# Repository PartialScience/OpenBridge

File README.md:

# OpenBridge

An open-source eight-IGBT full-bridge power stage for DRSSTC/Tesla-coil builds, designed in KiCad 10. It uses an external gate driver and DC supply, with two off-board gate-drive transformers and a Wakefield 511-6M heatsink.

| Schematic | PCB layout |
| :---: | :---: |
|  |  |

The 3D preview shows the main board after removing the four breakaway GDT strips. The PCB layout shows the complete fabrication board, with blue bottom copper beneath red top copper. Click either drawing for the full-size view.

## Project files

Open **[OpenBridge.kicad_pro](OpenBridge.kicad_pro)** in KiCad 10 or newer with the standard symbol, footprint and 3D-model libraries installed. Custom parts and STEP models are included in `OpenBridge.pretty`, `OpenBridge.kicad_sym` and `OpenBridge.3dshapes`.

The [Hardware subsheet](Hardware.kicad_sch) collects the heatsink, IGBT insulators, shoulder washers, spacers, cable connectors and assembly hardware. See its [drawing](docs/images/hardware.svg), the [BOM for one board](docs/bom.csv), and [assembly/BOM notes](docs/assembly.md).

GDT winding details, wire sizes, fastener lengths and other coil-dependent choices are **unspecified**. The BOM includes generic assembly materials; it does not define a complete coil, gate driver, power supply, fan or enclosure. Component ratings are not a validated operating rating for the assembled bridge.

## PCB fabrication

Fabrication specification for JLCPCB. Physical parameters are saved in `OpenBridge.kicad_pcb` under **Board Setup → Board Stackup → Physical Stackup / Board Finish**; via tenting is under **Solder Mask/Paste**.

| Setting | Specification |
| --- | --- |
| Construction | 2-layer FR-4, Tg135, 1.6 mm overall thickness |
| Copper | 2 oz on both sides, modeled as 0.070 mm (70 µm) per layer |
| Solder mask / silkscreen | Black / white |
| Surface finish | HASL with lead (`HAL SnPb` in KiCad) |
| Via covering | Tented on both sides |
| Nominal board outline | 116.84 × 167.64 mm, defined by Edge.Cuts |

Manufacturing requirements: **IPC Class 2**, **full flying-probe electrical testing**, and **±0.2 mm outline tolerance**. Select these with the fabricator when ordering.

The nominal stackup models a 1.44 mm FR-4 core and 0.01 mm solder mask per side. Dielectric constant (4.5) and loss tangent (0.02) are estimates pending manufacturer laminate data. Confirm the copper weight, laminate grade and finish with the fabricator.

## Update the previews

With Python 3.10+ and KiCad 10+ installed, run from the repository:

```sh
python scripts/update_previews.py
```

This audits the BOM and regenerates all README images from the saved design. Add `--watch` to refresh after saves while editing. The script uses a temporary board copy and isolated rendering settings, so it does not modify the manufacturing PCB or global KiCad preferences.

Set `board_color` in **[scripts/render-config.json](scripts/render-config.json)** to change the 3D solder mask. It defaults to `Black`; named KiCad colors and `#RRGGBB` are supported. The same file controls camera angle, image size and breakaway-strip removal. Run the script again after changing it.

KiCad is found automatically on Windows or through `PATH`. Set `KICAD_CLI` if needed, and `KICAD10_3DMODEL_DIR` if the standard models are installed elsewhere. Run `python scripts/check_bom.py` for the BOM audit/export alone.

The included [GitHub workflow](.github/workflows/previews.yml) refreshes and commits images/BOM after design changes are pushed to `main`, using the [official KiCad container](https://www.kicad.org/download/docker/). It needs Actions enabled and permission to push generated files; with branch protection, regenerate locally and include them in your normal review. The checked-in images also work offline.

## Contributing and license

Keep the schematic as the source of truth for parts, update the PCB from it when needed, and regenerate previews/BOM with design changes. Run KiCad ERC and DRC before proposing a change, and review all findings before fabrication. See the [assembly notes](docs/assembly.md) for component selection and validation guidance.

See [LICENSE](LICENSE) for the repository's GPL-3.0 license. Third-party libraries, datasheets and manufacturer models retain their applicable terms.

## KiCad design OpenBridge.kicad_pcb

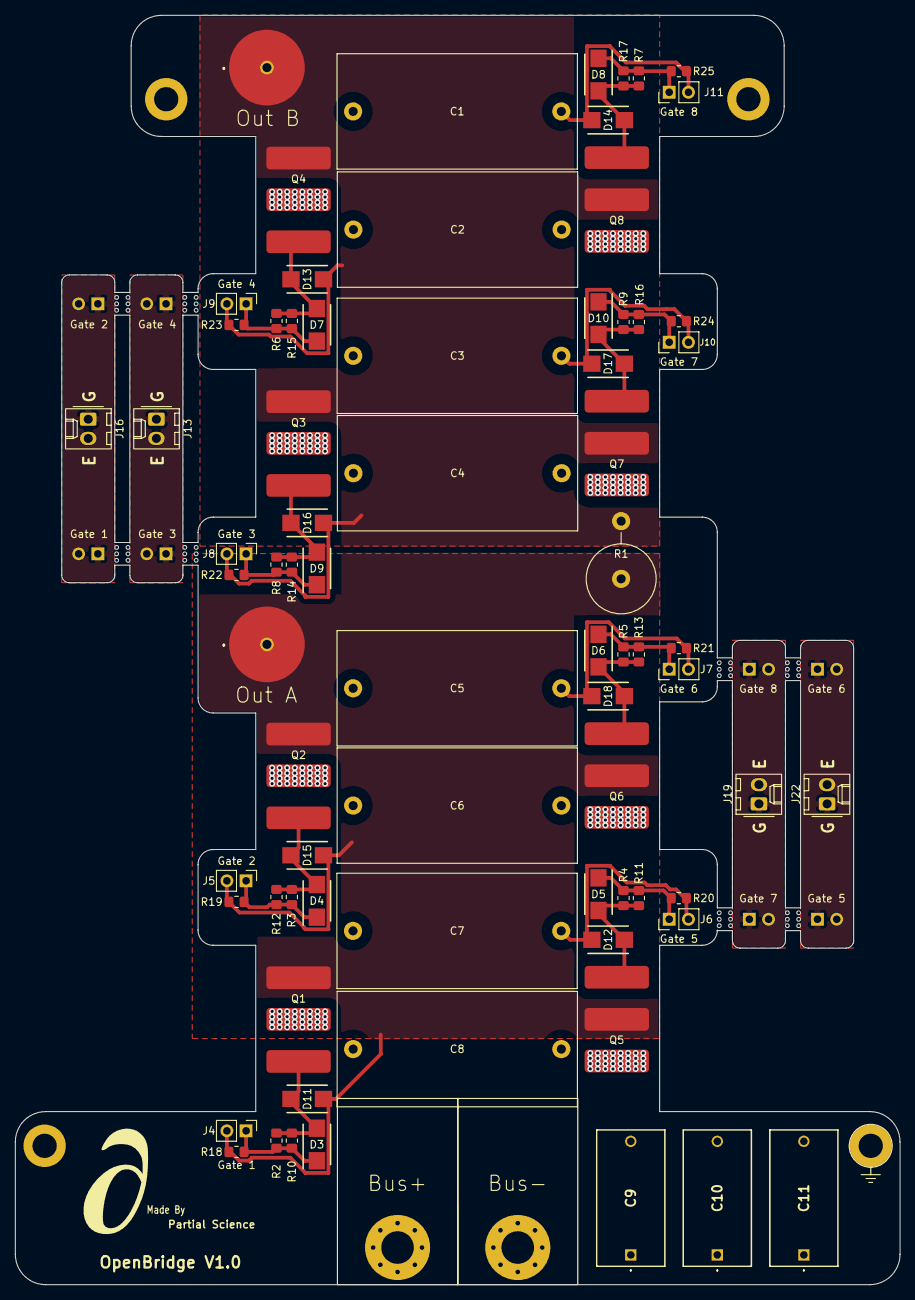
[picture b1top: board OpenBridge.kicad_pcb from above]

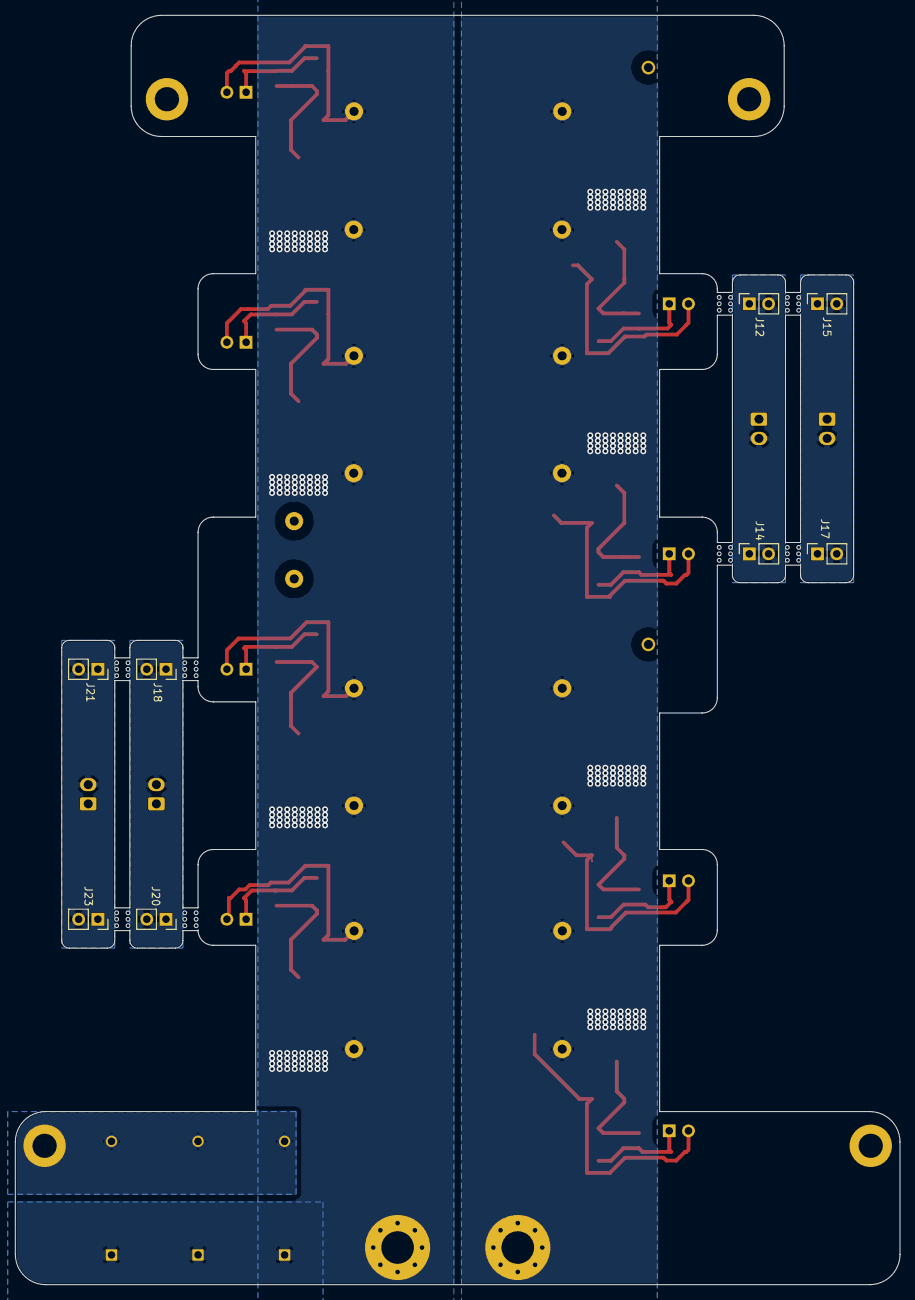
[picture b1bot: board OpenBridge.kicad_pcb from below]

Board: 2 copper layers, 116.8 x 167.6 mm, 105 parts (8 on the bottom side), 29 nets.

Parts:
C1, C2, C3, C4, C5, C6, C7, C8: 7uF; C_Rect_L31.5mm_W15.0mm_P27.50mm_KEMET_C4AQ
C9, C10, C11: 4.7nF; C_Rect_L18.0mm_W9.0mm_P15.00mm_TDK_B81123
D3, D4, D5, D6, D7, D8, D9, D10: SSB44; DIOM5436X265N
D11, D12, D13, D14, D15, D16, D17, D18: SMBJ24CA; DIONM5336X265N
H1, H2: MountingHole_Pad; MountingHole_4.3mm_M4_Pad_Via
H5, H6, H7, H8: MountingHole_Pad; MountingHole_3.2mm_M3_DIN965_Pad
HS1: 511-6M; Heatsink_Wakefield_511-6M
J1, J2: 7466105
J4, J5, J6, J7, J8, J9, J10, J11: Conn_01x02; PinHeader_1x02_P2.54mm_Vertical
J12, J14, J15, J17, J18, J20, J21, J23: Conn_01x02; PinSocket_1x02_P2.54mm_Vertical
J13, J16, J19, J22: Conn_01x02; Molex_KK-254_AE-6410-02A_1x02_P2.54mm_Vertical
MB1, MB2, MB3, MB4, MB5, MB6, MB7, MB8, MB9, MB10, MB11, MB12, MB13, MB14, MB15, MB16: MouseBite; BreakLine_3h_D0.5mm_P0.85mm
Q1, Q2, Q3, Q4, Q5, Q6, Q7, Q8: FGH75T65SHD-F155; TO-247-3_onsemi-340CH_Horizontal_TabUp_ScrewAccess
R1: 10k; R_Axial_DIN0922_L20.0mm_D9.0mm_P7.62mm_Vertical
R2, R3, R4, R5, R6, R7, R8, R9, R10, R11, R12, R13, R14, R15, R16, R17: 9.1; R_0805_2012Metric_Pad1.20x1.40mm_HandSolder
R18, R19, R20, R21, R22, R23, R24, R25: 10k; R_0805_2012Metric_Pad1.20x1.40mm_HandSolder

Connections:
/BS1_E: J12.2, J13.2, J14.2
/BS1_G: J12.1, J13.1, J14.1
/BS2_E: J15.2, J16.2, J17.2
/BS2_G: J15.1, J16.1, J17.1
/BS3_E: J18.2, J19.2, J20.2
/BS3_G: J18.1, J19.1, J20.1
/BS4_E: J21.2, J22.2, J23.2
/BS4_G: J21.1, J22.1, J23.1
/Bus+: C1.1, C2.1, C3.1, C4.1, C5.1, C6.1, C7.1, C8.1, H1.1 (1_1), Q1.2 (C), Q2.2 (C), Q3.2 (C), Q4.2 (C)
/Bus-: C1.2, C2.2, C3.2, C4.2, C5.2, C6.2, C7.2, C8.2, C9.1, C10.1, C11.1, D12.1 (A1), D14.1 (A1), D17.1 (A1), D18.1 (A1), H2.1 (1_1), J6.2, J7.2, J10.2, J11.2, Q5.3 (E), Q6.3 (E), Q7.3 (E), Q8.3 (E), R20.1, R21.2, R24.1, R25.2
/G1: D3.2 (A), D11.2 (A2), Q1.1 (G), R2.2, R10.2
/G2: D4.2 (A), D15.2 (A2), Q2.1 (G), R3.2, R12.2
/G3: D9.2 (A), D16.2 (A2), Q3.1 (G), R8.1, R14.1
/G4: D7.2 (A), D13.2 (A2), Q4.1 (G), R6.1, R15.1
/G5: D5.2 (A), D12.2 (A2), Q5.1 (G), R4.2, R11.2
/G6: D6.2 (A), D18.2 (A2), Q6.1 (G), R5.2, R13.2
/G7: D10.2 (A), D17.2 (A2), Q7.1 (G), R9.1, R16.1
/G8: D8.2 (A), D14.2 (A2), Q8.1 (G), R7.1, R17.1
/GDT1_A: D3.1 (K), J4.1, R2.1, R10.1, R18.2
/GDT2_A: D7.1 (K), J9.1, R6.2, R15.2, R23.1
/GDT3_A: D5.1 (K), J6.1, R4.1, R11.1, R20.2
/GDT4_A: D8.1 (K), J11.1, R7.2, R17.2, R25.1
/OutA: D11.1 (A1), D15.1 (A1), J1.1 (Pin_1_1), J4.2, J5.2, Q1.3 (E), Q2.3 (E), Q5.2 (C), Q6.2 (C), R1.1, R18.1, R19.2
/OutB: D13.1 (A1), D16.1 (A1), J2.1 (Pin_1_1), J8.2, J9.2, Q3.3 (E), Q4.3 (E), Q7.2 (C), Q8.2 (C), R1.2, R22.1, R23.2
Heat Sink: C9.2, C10.2, C11.2, H5.1 (1_1)
unnamed: D4.1 (K), J5.1, R3.1, R12.1, R19.1
unnamed: D6.1 (K), J7.1, R5.1, R13.1, R21.1
unnamed: D9.1 (K), J8.1, R8.2, R14.2, R22.2
unnamed: D10.1 (K), J10.1, R9.2, R16.2, R24.2

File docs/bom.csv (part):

References,Quantity,Value,Manufacturer,MPN,Footprint,Description,Mouser,Datasheet
"C1, C2, C3, C4, C5, C6, C7, C8",8,7uF,KEMET,C4AQCBU4700A1YJ,OpenBridge:C_Rect_L31.5mm_W15.0mm_P27.50mm_KEMET_C4AQ,"Film capacitor, 7 uF 5 %, 650 VDC, metallized polypropylene DC-link, 27.5 mm pitch, 14 x 28 x 31.5 mm (KEMET C4AQ). Bridge bus decoupling",80-C4AQCBU4700A1YJ,https://www.mouser.com/datasheet/3/508/1/KEM_F3114_C4AQ.pdf
"C9, C10, C11",3,4.7nF,TDK,B81123C1472M000,OpenBridge:C_Rect_L18.0mm_W9.0mm_P15.00mm_TDK_B81123,"Y1 safety capacitor, 4.7 nF 20 %, 500 VAC, MKP film, 15 mm pitch, 9.0 x 17.5 x 18.0 mm (TDK B81123). Bus negative to RF ground. M000 = untaped, 6 mm leads; M289 is the same part on ammo tape",871-B81123C1472M,https://www.tdk-electronics.tdk.com/inf/20/20/db/fc_2009/Y1_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
"D3, D4, D5, D6, D7, D8, D9, D10",8,SSB44,Taiwan Semiconductor,SSB44,OpenBridge:DIOM5436X265N,"Schottky rectifier, 40 V, 4 A, SMB (DO-214AA). Pin 1 = K, pin 2 = A",821-SSB44,https://www.taiwansemi.com/assets/uploads/datasheet/SSB44_B2102.pdf
"D11, D12, D13, D14, D15, D16, D17, D18",8,SMBJ24CA,SEMTECH,SMBJ24CA,OpenBridge:DIONM5336X265N,"Bidirectional TVS diode, 24 V standoff, 600 W, SMB (DO-214AA). ESD Suppressors / TVS Diodes 1-Line 24V 15.4A TVS",947-SMBJ24CA,https://semtech.my.salesforce.com/sfc/p/E0000000JelG/a/2R000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
HS1,1,511-6M,Wakefield Thermal,511-6M,OpenBridge:Heatsink_Wakefield_511-6M,"Wakefield 511-6M aluminum heatsink, 152.4 mm long; board mounted on 3 mm spacers. Project STEP model and mechanical envelope; no PCB pads.",567-511-6M,https://wakefieldthermal.com/content/data_sheets/2021_data_s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
"HW1, HW2, HW3, HW4, HW5, HW6",6,22-01-2027,Molex,22-01-2027,,"KK 254 crimp housing 1x02, 2.54 mm, with friction ramp (Molex 2695). Wire-side mate of the GDT headers J13/J16/J19/J22",538-22-01-2027,
"HW7, HW8, HW9, HW10, HW11, HW12, HW13, HW14, HW15, HW16, HW17, HW18",12,08-50-0114,Molex,08-50-0114,,"KK 254 crimp terminal, female, 22-30 AWG, tin (Molex 2759). 2 per KK housing; buy spares for crimping",538-08-50-0114,
"HW19, HW20, HW21, HW22, HW23, HW24, HW25, HW26",8,60-11-D401-1671,Parker Chomerics,60-11-D401-1671,,"Thermal insulator pad, TO-247, 1.41 x 0.81 in, 0.015 in thick (Chomerics). 1 per IGBT (Q1-Q8)",24-60-11-D401-1671,
"HW27, HW28, HW29, HW30",4,M0592-3-N,RAF Electronic Hardware,M0592-3-N,,"Round spacer, M3 (3.2 mm ID), 3 mm long (RAF). Board to heat sink at H5-H8",761-M0592-3-N,
"HW31, HW32, HW33, HW34, HW35, HW36, HW37, HW38",8,3049,Keystone Electronics,3049,,"Shoulder washer #4, nylon 6/6 (Keystone 3049): 2.9 mm ID, 3.43 mm shoulder, 5.5 mm flange. Insulates each IGBT's 4-40 screw from its collector tab",534-3049,https://www.mouser.com/datasheet/3/201/1/3049.pdf
"HW39, HW40, HW41, HW42, HW43, HW44, HW45, HW46",8,#4-40 screw,Generic,Unspecified,,"IGBT-to-heatsink screw, #4-40; one per Q1-Q8, used with HW31-HW38 shoulder washers. Length, head style and tapped-hole depth unspecified; select for the assembled stack.",,
"HW47, HW48, HW49, HW50",4,M3 screw,Generic,Unspecified,,"Board-to-heatsink screw, M3; one per H5-H8 with 3 mm spacers. Length and head style unspecified; select for PCB thickness, spacer and tapped-hole engagement.",,
"HW51, HW52",2,M5 screw,Generic,Unspecified,,"Output ring-lug clamp screw, M5, one per J1/J2. Length unspecified; choose for lug/washer stack and <=4 mm thread engagement without bottoming in the REDCUBE blind hole.",,
"HW53, HW54",2,M5 flat washer,Generic,Unspecified,,"Flat washer, M5, one per J1/J2 output ring-lug clamp. Material and outside diameter unspecified.",,
"HW55, HW56",2,M5 ring terminal,Generic,Unspecified,,"Output cable ring terminal, M5 stud, one per J1/J2. Wire gauge, current rating and insulation unspecified; select for the coil build.",,
HW57,1,Power wire (lot),Generic,Unspecified,,"One assembly lot of power cable. Conductor gauge, insulation rating, length and termination details unspecified; selected for the coil build.",,
"HW58, HW59",2,M4 bolt,Generic,Unspecified,,"DC-input ring-lug clamp bolt, M4, one per H1/H2. Bolt length and head style unspecified; select for lug, PCB and washer stack.",,
"HW60, HW61",2,M4 nut,Generic,Unspecified,,"Nut, M4, one per H1/H2 DC-input bolt. Material and locking method unspecified.",,
"HW62, HW63, HW64, HW65",4,M4 flat washer,Generic,Unspecified,,"Flat washer, M4, two per H1/H2 DC-input bolt to distribute clamp load. Outside diameter and material unspecified.",,
"HW66, HW67",2,M4 ring terminal,Generic,Unspecified,,"DC-input cable ring terminal, M4 stud, one per H1/H2. Wire gauge, current rating and insulation unspecified; select for the coil build.",,
HW68,1,GDT wire (lot),Generic,Unspecified,,"One assembly lot of GDT winding and lead wire for T1/T2. Turns, ratio, phasing, wire gauge, insulation and length unspecified; selected for the coil build. T1/T2 BOM entries supply the bare cores only.",,
HW69,1,Insulation (lot),Generic,Unspecified,,"One assembly lot of heat-shrink/insulating sleeving for wiring and terminations. Material, insulation rating, sizes and length unspecified; selected for the coil build.",,
"J1, J2",2,7466105,Wurth Elektronik,7466105,OpenBridge:7466105,"REDCUBE WP-SMBU SMT bush, M5 blind thread 4 mm deep, 9 mm dia, 7 mm high (7.8 mm with locating pin), 70 A, tin-plated brass (Wurth). Ring-lug connection for the inverter outputs; nothing protrudes under the board",710-7466105,https://www.we-online.com/catalog/datasheet/7466105.pdf
"J4, J5, J6, J7, J8, J9, J10, J11",8,Conn_01x02,Wurth Elektronik,61300211121,Connector_PinHeader_2.54mm:PinHeader_1x02_P2.54mm_Vertical,"Male pin header 1x02, 2.54 mm, vertical THT (Wurth WR-PHD). Gate/emitter pins for a bridge strip",710-61300211121,
J12,1,Conn_01x02,Wurth Elektronik,61300211821,Connector_PinSocket_2.54mm:PinSocket_1x02_P2.54mm_Vertical,"Female socket header 1x02, 2.54 mm, vertical THT (Wurth WR-PHD). GDT bridge strip BS1: end (upper header pair)",710-61300211821,
J13,1,Conn_01x02,Molex,171856-0002,Connector_Molex:Molex_KK-254_AE-6410-02A_1x02_P2.54mm_Vertical,"KK 254 header 1x02, 2.54 mm, vertical THT, friction ramp (Molex 171856). GDT bridge strip BS1: GDT twisted pair",538-171856-0002,
J14,1,Conn_01x02,Wurth Elektronik,61300211821,Connector_PinSocket_2.54mm:PinSocket_1x02_P2.54mm_Vertical,"Female socket header 1x02, 2.54 mm, vertical THT (Wurth WR-PHD). GDT bridge strip BS1: end (lower header pair)",710-61300211821,
J15,1,Conn_01x02,Wurth Elektronik,61300211821,Connector_PinSocket_2.54mm:PinSocket_1x02_P2.54mm_Vertical,"Female socket header 1x02, 2.54 mm, vertical THT (Wurth WR-PHD). GDT bridge strip BS2: end (upper header pair)",710-61300211821,
J16,1,Conn_01x02,Molex,171856-0002,Connector_Molex:Molex_KK-254_AE-6410-02A_1x02_P2.54mm_Vertical,"KK 254 header 1x02, 2.54 mm, vertical THT, friction ramp (Molex 171856). GDT bridge strip BS2: GDT twisted pair",538-171856-0002,
J17,1,Conn_01x02,Wurth Elektronik,61300211821,Connector_PinSocket_2.54mm:PinSocket_1x02_P2.54mm_Vertical,"Female socket header 1x02, 2.54 mm, vertical THT (Wurth WR-PHD). GDT bridge strip BS2: end (lower header pair)",710-61300211821,
J18,1,Conn_01x02,Wurth Elektronik,61300211821,Connector_PinSocket_2.54mm:PinSocket_1x02_P2.54mm_Vertical,"Female socket header 1x02, 2.54 mm, vertical THT (Wurth WR-PHD). GDT bridge strip BS3: end (upper header pair)",710-61300211821,
J19,1,Conn_01x02,Molex,171856-0002,Connector_Molex:Molex_KK-254_AE-6410-02A_1x02_P2.54mm_Vertical,"KK 254 header 1x02, 2.54 mm, vertical THT, friction ramp (Molex 171856). GDT bridge strip BS3: GDT twisted pair",538-171856-0002,
J20,1,Conn_01x02,Wurth Elektronik,61300211821,Connector_PinSocket_2.54mm:PinSocket_1x02_P2.54mm_Vertical,"Female socket header 1x02, 2.54 mm, vertical THT (Wurth WR-PHD). GDT bridge strip BS3: end (lower header pair)",710-61300211821,
J21,1,Conn_01x02,Wurth Elektronik,61300211821,Connector_PinSocket_2.54mm:PinSocket_1x02_P2.54mm_Vertical,"Female socket header 1x02, 2.54 mm, vertical THT (Wurth WR-PHD). GDT bridge strip BS4: end (upper header pair)",710-61300211821,
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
